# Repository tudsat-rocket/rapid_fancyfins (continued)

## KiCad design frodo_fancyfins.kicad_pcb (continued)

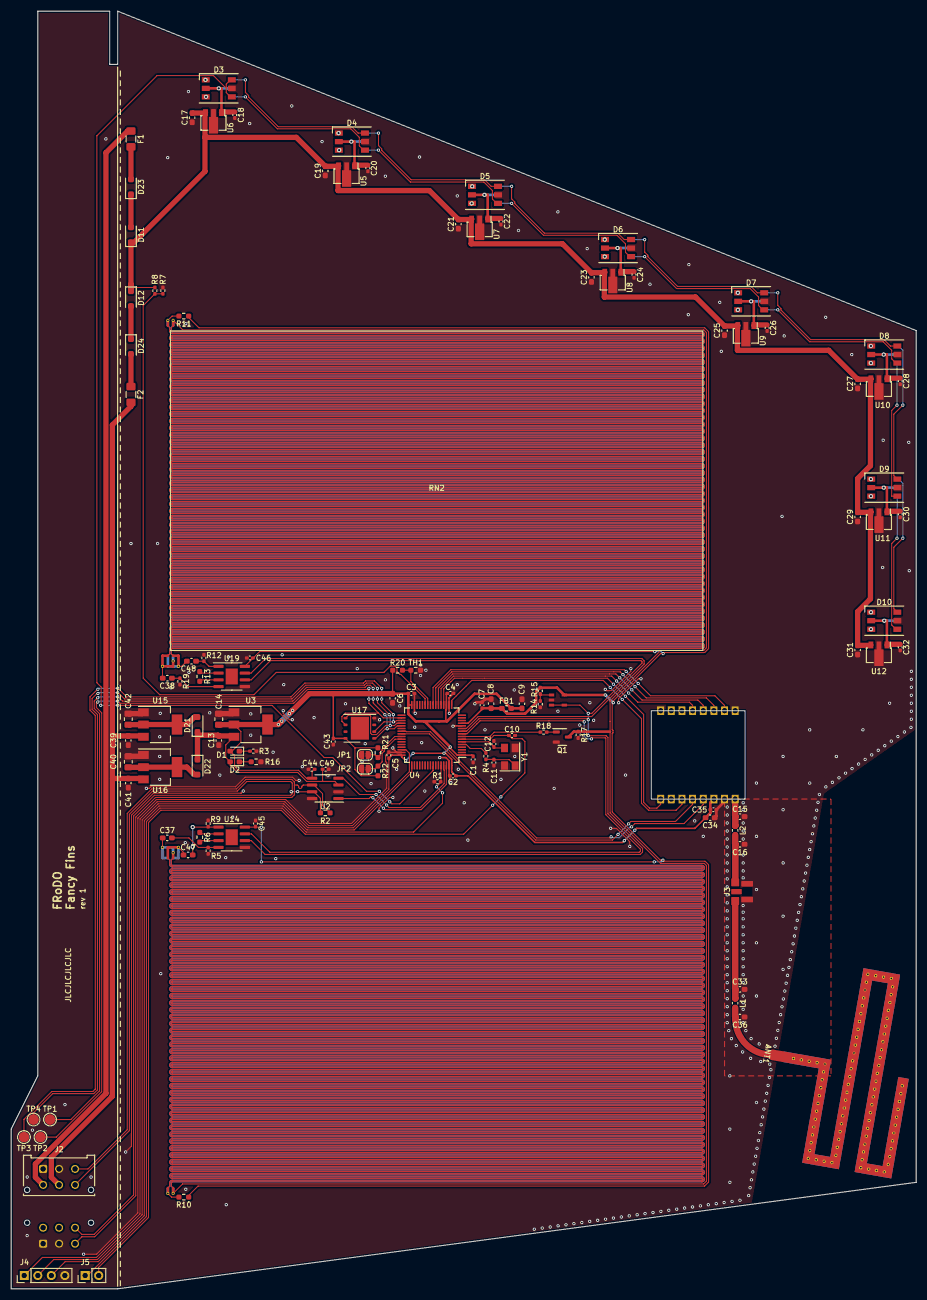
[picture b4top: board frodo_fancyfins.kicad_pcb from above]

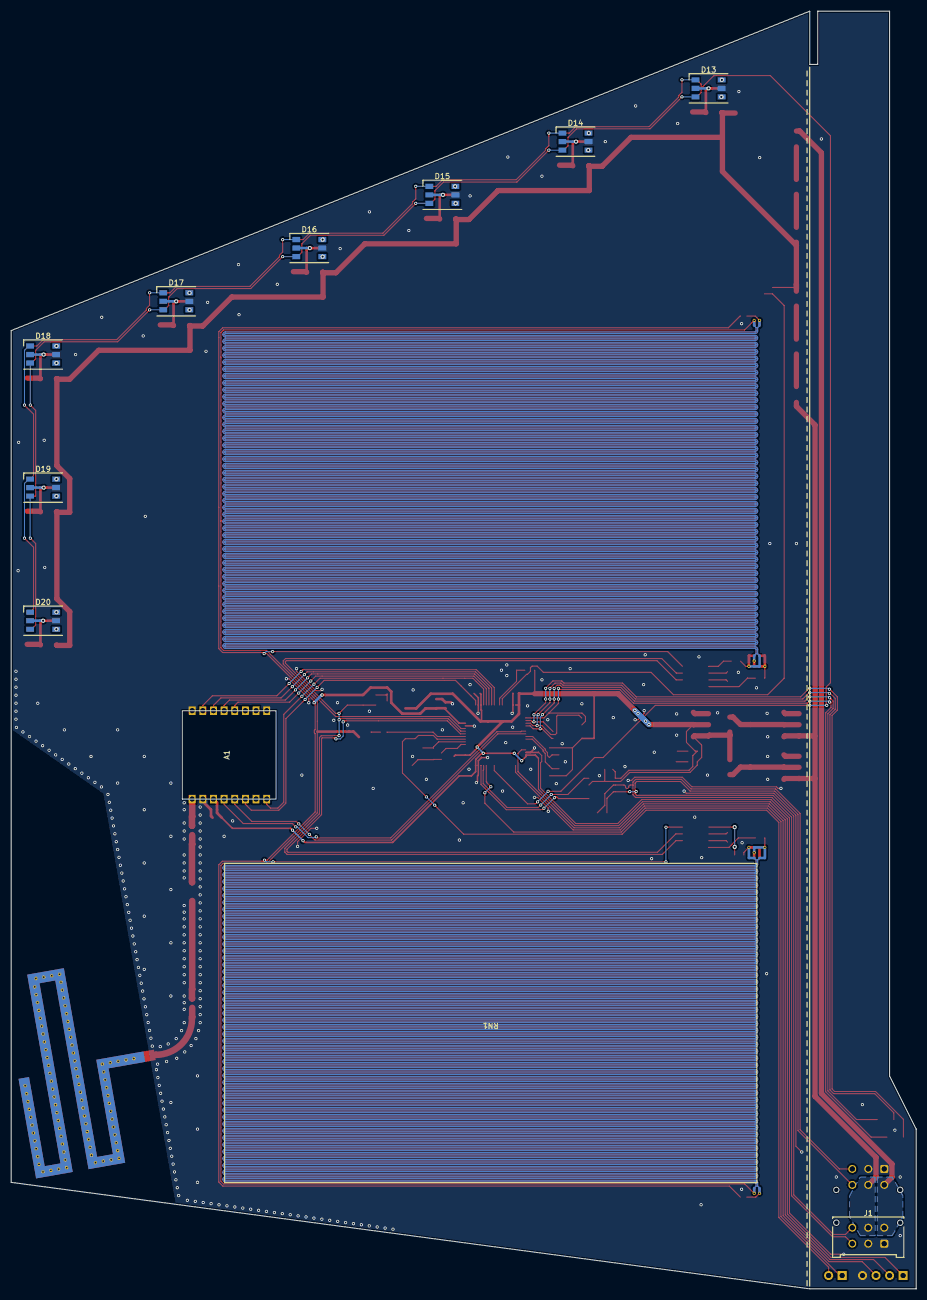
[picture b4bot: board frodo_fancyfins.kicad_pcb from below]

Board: 2 copper layers, 170.0 x 240.0 mm, 135 parts (11 on the bottom side), 114 nets.

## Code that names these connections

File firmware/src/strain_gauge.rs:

use embassy_embedded_hal::flash;
use embassy_executor;
use embassy_stm32::adc::Adc;
use embassy_stm32::gpio::{Output, Level, Speed};
use embassy_stm32::pac::WRITE_SIZE;
use embassy_stm32::spi::{Config, Phase, Polarity, Spi};
use embassy_stm32::time::Hertz;
use embassy_stm32::peripherals::*;
use embassy_time::{with_timeout, Delay, Duration, Ticker, Timer};
use shared_types::FlightMode;
use smart_leds::RGB8;
use w25q::prelude;
use w25q::series25::Flash;
use ws2812_spi::Ws2812;
use smart_leds::SmartLedsWrite;

use crate::FlightModeSubscriber;

fn to_millivolts(vref_sample: u16, sample: u16) -> u16 {
    const VREFINT_MV: u32 = 1200; // mV
    (u32::from(sample) * VREFINT_MV / u32::from(vref_sample)) as u16
}

#[embassy_executor::task]
pub async fn run(
    mut adc: Adc<'static, ADC1>,
    sg_en_pin: PC0,
    mut sg_vout0_pin: PC1,
    mut _sg_ref_pin: PC2,
    mut sg_vout1_pin: PC3,
    mut flight_mode_subscriber: crate::can::FlightModeSubscriber,
    spi: SPI2,
    cs: PC6,
    sck: PB13,
    miso: PB14,
    mosi: PB15,
    dma_out: DMA1_CH5,
    dma_in: DMA1_CH4
) -> ! {

    /*** Commented out for testing
    // do not start recording until shortly before launch
    let mut fm = FlightMode::default();

    while fm < FlightMode::ArmedLaunchImminent {
        if let Some(new_fm) = flight_mode_subscriber.try_next_message_pure() {
            defmt::println!("{:?}", defmt::Debug2Format(&new_fm));
            fm = new_fm;
        }
    }
    ***/

    const TIMEOUT: Duration = Duration::from_micros(100);

    let mut enable = Output::new(sg_en_pin, Level::Low, Speed::Low);

    // 2000 Hz
    let mut ticker = Ticker::every(Duration::from_micros(50000));

    let mut config = Config::default();
    config.frequency = Hertz::mhz(2);
    let mut spi_bus = embassy_stm32::spi::Spi::new(spi, sck, mosi, miso, dma_out, dma_in, config);
    let mut cs = Output::new(cs, Level::High, Speed::Low);
    let mut flash = Flash::init(spi_bus, cs).unwrap();

    if let Ok(info)= flash.get_device_info(){
        defmt::println!("Flash recognized as {:?} with {:?} kb", info.id, info.capacity_kb);
    }
    
    if let Err(_e) = flash.write_enable(){
        defmt::println!("Flash write enable error");
    }

    let mut i = 0;
    let mut addr = 0;
    const WRITE_SIZE: usize = 4;
    let mut data: [u8; WRITE_SIZE] = [0x00,0x00,0x00,0x00];
    loop {
        enable.set_high();
        let sg_ref_sample = with_timeout(TIMEOUT, adc.read(&mut _sg_ref_pin)).await.unwrap_or_default();
        let sg_vout0_sample = with_timeout(TIMEOUT, adc.read(&mut sg_vout0_pin)).await.unwrap_or_default();
        let sg_vout1_sample = with_timeout(TIMEOUT, adc.read(&mut sg_vout1_pin)).await.unwrap_or_default();
        enable.set_low();

        i += 1;
        if i > 100 {
            defmt::println!("[SG] {:?} {:?}", sg_vout0_sample, sg_vout1_sample);
            i = 0;
        }

        let sg_vout0_voltage = to_millivolts(sg_ref_sample, sg_vout0_sample);
        let sg_vout1_voltage = to_millivolts(sg_ref_sample, sg_vout1_sample);

        /***
        cs.set_low();
        Timer::after(Duration::from_micros(100)).await;
        let mut read: [u8; 4] = [0x00, 0x00, 0x00, 0x00];
        let mut write: [u8; 4] = [0x9f, 0x00, 0x00, 0x00];
        let res = spi_bus.transfer(&mut read, &write).await.unwrap();
        Timer::after(Duration::from_micros(100)).await;
        cs.set_high();
        defmt::println!("{:?} {:?}", read, write);
        ***/

        let v0 = sg_vout0_voltage.to_le_bytes();
        let v1 = sg_vout1_voltage.to_le_bytes();

        data[0] = v0[0];
        data[1] = v0[1];
        data[2] = v1[0];
        data[3] = v1[1];

        if let Err(_e) = flash.write_bytes(addr, &mut data){
            defmt::println!("Flash write error");
        }
        
        addr += WRITE_SIZE as u32;

        // TODO read strain gauge value and write to flash
        ticker.next().await;
    }
}

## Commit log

2023-12-28 File structure cleanup
2024-01-17 Add INA826, antenna symbol and antenna footprint
2024-01-17 Add RGB LED schematics
2024-01-17 Schematics cleanup
2024-01-18 Create symbol and footprint of RF module
2024-01-18 Add RF module to Schematics
2024-01-20 Add strain gauge schematics
2024-01-24 3.3V and 5V power supply tweaks
2024-01-25 Add commentary concerning power supply
2024-01-25 Add flash memory schematics
2024-01-26 Asign footprints, add missing footprints, adjust Rext.
2024-01-30 Switch from STM32F072 to STM32F103, Add fin shape draft, Place component footprints
2024-02-01 PCB Layout (traces, edge cuts, silk screen, 3d models)
2024-02-01 Minor changes for ordering
2024-07-31 implement changes from rev 0 to rev 1
2024-07-31 add LCSC part numbers, tweak some footprints
2024-08-09 Add firmware skeleton
2024-08-11 Add flash crate
2024-08-11 Add .cargo/config.toml
2024-08-11 Fix build issues, handle flash stuff in fin_tasks
2024-08-12 Check flight mode for recording and led output
2024-08-17 Add initalization for led driver and flash driver
2024-08-20 Separate strain gauge and LED modules, implement flight mode signal
2024-08-20 Implement experimental data writing
2024-09-19 Implement strain-gauge-via-CAN
2025-03-25 added new leds, edge connectors and flexpcb
2025-04-08 finished layout, added a bunch of footprints, fixed outer form
2025-04-23 making sure most resent state is online
2025-04-24 changed fancyfins layout a bit; added local footprint library
2025-04-24 added fancy fins routing
2025-04-27 fixed some errors in the fancyfins pcb
2025-04-27 fixed led symbol
2025-04-27 changed fancyfinns pcb layout
2025-04-27 changed led routing
2025-04-27 changed led position
2025-04-27 changed scematic + examplary layout
2025-04-28 began fancyfin routing
2025-04-29 continued working on fancyfins routing
2025-04-29 fixed gnd issue
2025-04-29 added some vias for better gnd connection
2025-04-29 finalized fancyfin routing (for now)
2025-06-09 finished routing for fin board
2025-07-23 some changes according to manu, added connector board
